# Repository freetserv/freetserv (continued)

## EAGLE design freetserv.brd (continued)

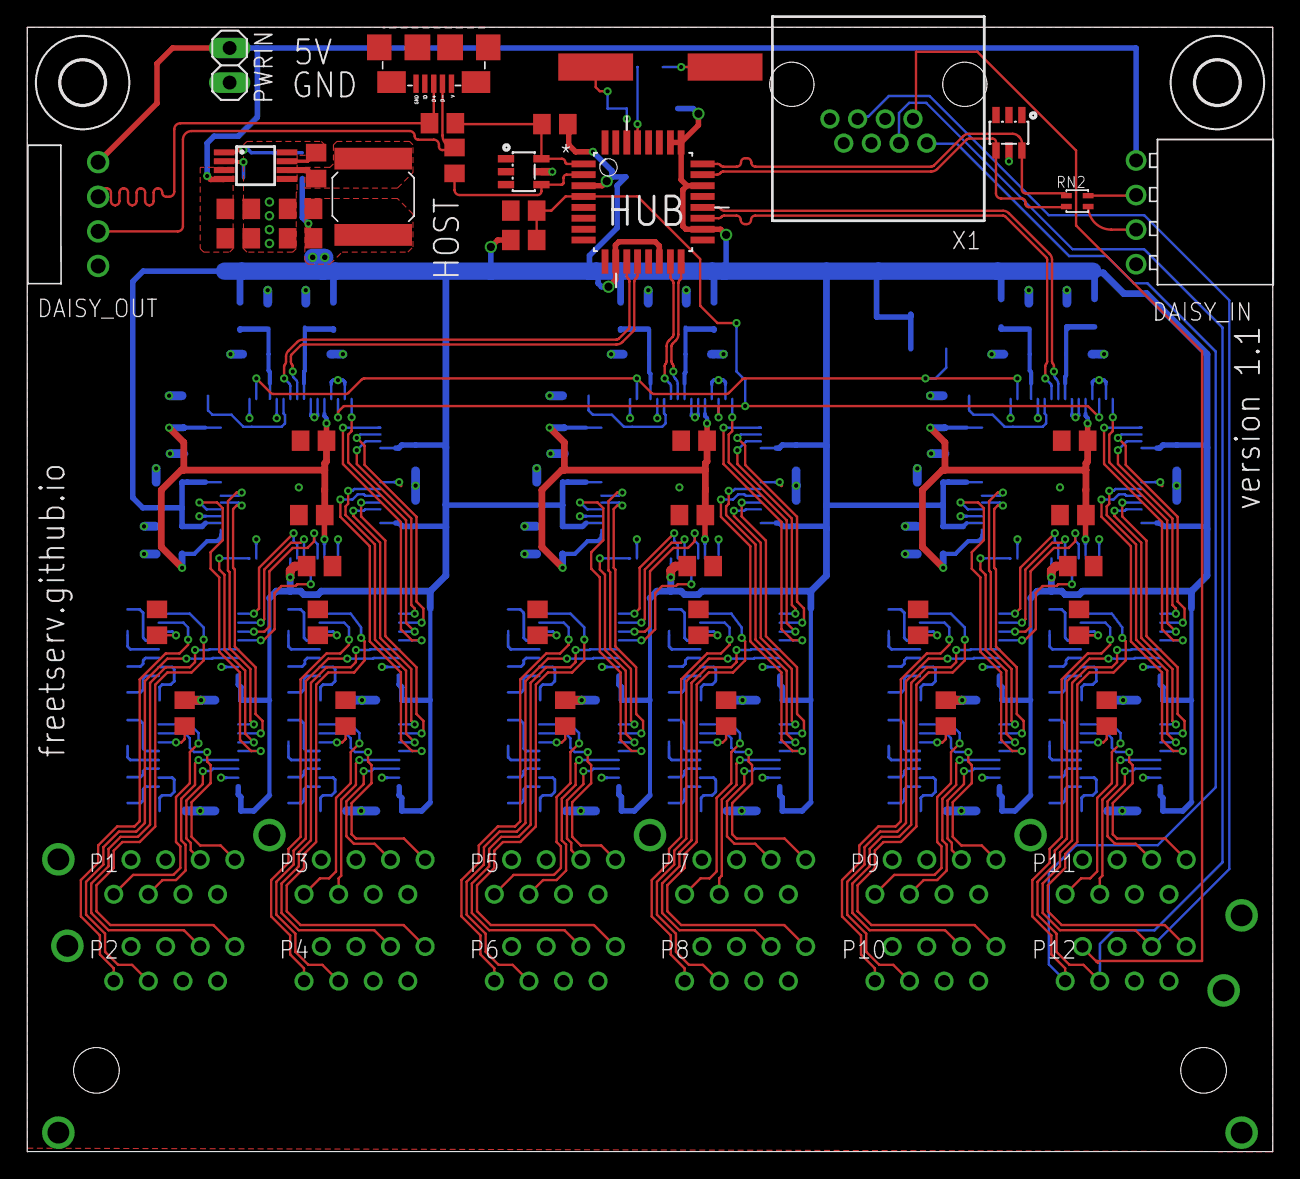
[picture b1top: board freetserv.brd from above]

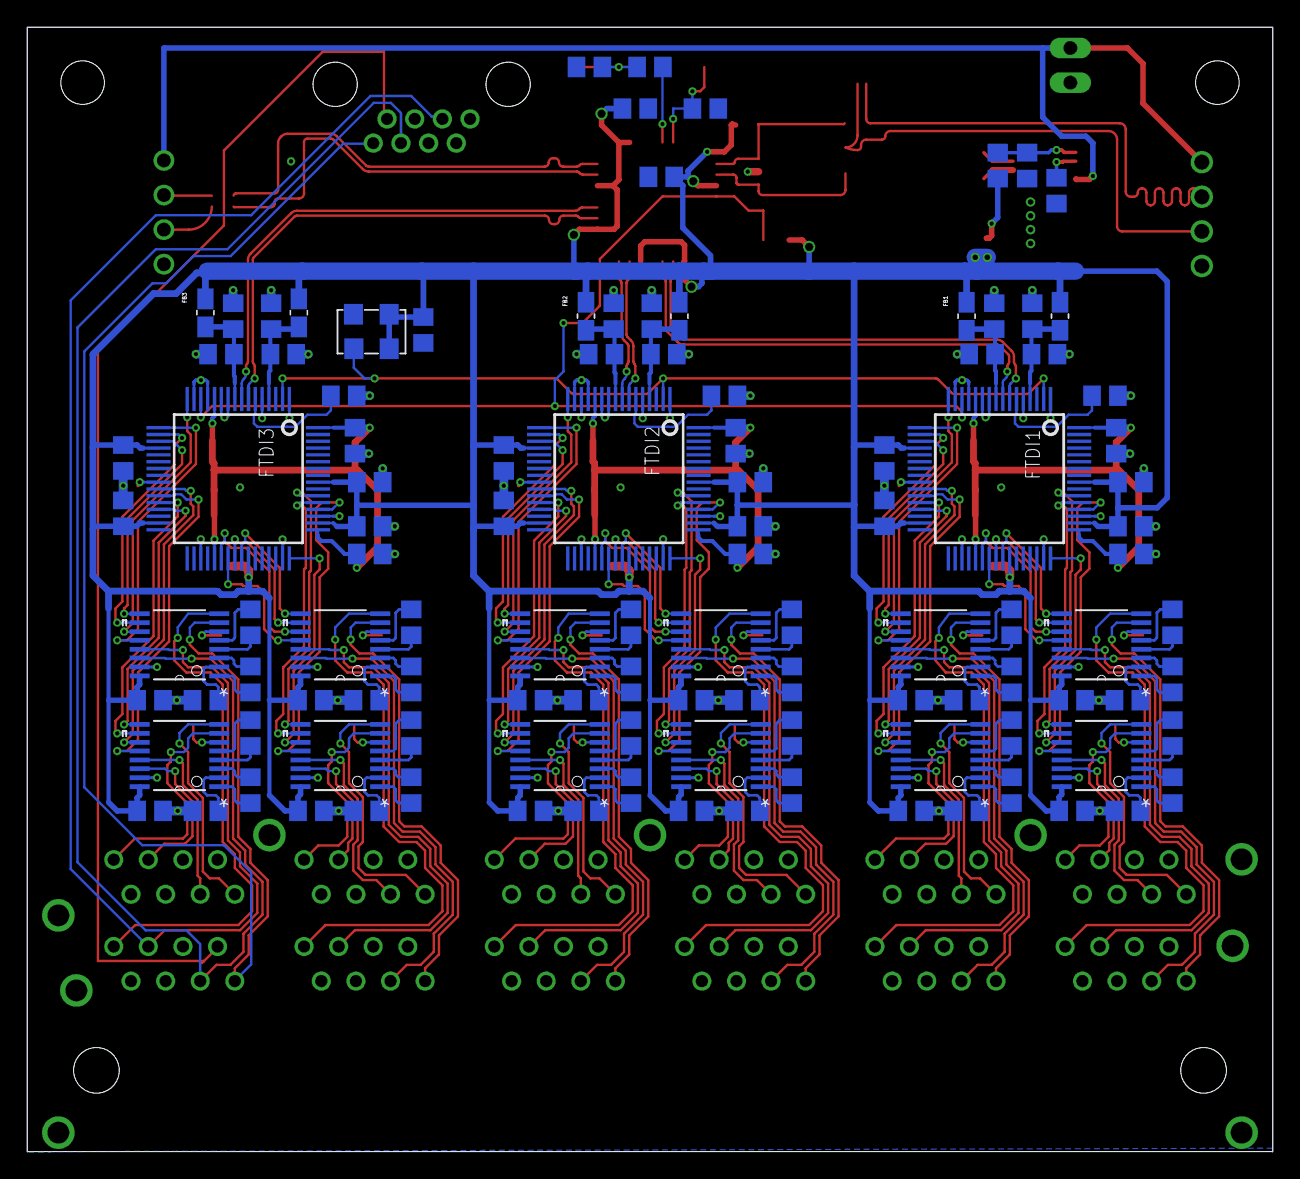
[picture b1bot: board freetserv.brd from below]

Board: 2 copper layers, 91.4 x 82.5 mm, 158 parts (112 on the bottom side), 207 nets.

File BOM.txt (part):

Qty Value              Part Num         Package               Parts                                                                                                                                                                                                                                                                                                                                                                                                                                                                                                       
1                      A1921-ND         1X02                  PWRIN                                                                                                                                                                                                                                                                                                                                                                                                                                                                                                       
95  0.1uF              1276-1003-1-ND   C0805                 C1, C4, C11, C12, C15, C16, C17, C18, C19, C22, C23, C24, C25, C26, C27, C28, C29, C30, C31, C32, C33, C34, C35, C36, C37, C38, C39, C40, C41, C42, C43, C44, C45, C46, C47, C54, C55, C56, C57, C58, C59, C60, C61, C62, C63, C64, C65, C66, C67, C68, C69, C70, C71, C72, C73, C74, C75, C76, C77, C78, C79, C80, C81, C89, C90, C91, C92, C93, C94, C95, C96, C97, C98, C99, C100, C101, C102, C103, C104, C105, C106, C107, C108, C109, C110, C111, C112, C113, C114, C115, C116, C489, C519, C859, C869
2   1.5K               311-1.5KARCT-ND  R0805                 R3, R6                                                                                                                                                                                                                                                                                                                                                                                                                                                                                                      
1   1uF                311-1365-1-ND    C0805                 C5                                                                                                                                                                                                                                                                                                                                                                                                                                                                                                          
3   3.3uF              445-7589-1-ND    C0805                 C8, C629, C829                                                                                                                                                                                                                                                                                                                                                                                                                                                                                              
6   4.7uF              1276-2972-1-ND   C0805                 C13, C14, C53, C502, C879, C889                                                                                                                                                                                                                                                                                                                                                                                                                                                                             
1   6MHz               535-10208-1-ND   CSM-7X-DU             Q2                                                                                                                                                                                                                                                                                                                                                                                                                                                                                                          
1   10k                311-10KARCT-ND   R0805                 R5                                                                                                                                                                                                                                                                                                                                                                                                                                                                                                          
4   10uF               490-10517-1-ND   C0805                 C2, C3, C6, C7                                                                                                                                                                                                                                                                                                                                                                                                                                                                                              
3   12K / 1%           311-12.0KCRCT-ND R0805                 R2, R13, R15                                                                                                                                                                                                                                                                                                                                                                                                                                                                                                
1   15uH               587-2624-1-ND    NR60XX                L3                                                                                                                                                                                                                                                                                                                                                                                                                                                                                                          
2   18pF               709-1171-1-ND    C0805                 C20, C21                                                                                                                                                                                                                                                                                                                                                                                                                                                                                                    
1   22K                311-22KARCT-ND   R0805                 R7                                                                                                                                                                                                                                                                                                                                                                                                                                                                                                          
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
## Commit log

2015-09-01 Initial commit, schematics mostly complete, layout still not done
2015-09-01 layouted power-related part, added more MAX3232 drivers to schematics
2015-09-01 layout all MAX3232s, position power distribution
2015-09-02 routed the MAX3232 and FT4232HL within final space constraints
2015-09-02 use TUSB2046B (+ additional USB port), route both
    Warnings need to be addressed, but the bulk of the routing should now be
    done.
2015-09-03 hook up the second USB port to the SN75240 as well
2015-09-03 make differential pairs more symmetric, move vias close to TUSB
    also add the recommended 0.1uF capacitor close to the power pin
2015-09-03 fix GND plane vias for power USB ports
2015-09-03 fix all clearance DRC warnings (with smart-prototyping DRU file)
2015-09-03 make all vias at least 12mil (minimum smart-prototyping size)
2015-09-03 address all DRC warnings
2015-09-03 add ground planes underneath the crystals
2015-09-03 route the USB data tracks underneath the 3.3V
    That way, we have identical distortions on both lines, and they are
    further away from the voltage regulator.
2015-09-03 add labels to the USB ports
2015-09-03 add .gitignore to ignore EAGLE’s temporary files
2015-09-03 add gerber files for smart-prototyping.com
2015-09-22 renamed L1, L2 to FERRITE1, FERRITE2, added values
2015-09-26 Bugfix: add 1.5kΩ resistor to USB D+ to host
    This is necessary for the host to recognize that a USB device was
    plugged in. Without this resistor, nothing happens when you connect the
    board to a computer.
2015-09-26 Replace all 100nF capacitors with 0.1uF (which is the same)
    Since capacitors are labelled as 0.1uF, this makes it more clear which
    part goes where.
    fixes #8
2015-09-26 use 18pF capacitors to match the crystals
2015-09-26 assign part numbers for almost all parts
    The remaining parts are possibly subject to change.
    This was done using the bom-ex ULP:
    http://www.cadsoftusa.com/downloads/file/bom-ex164.zip
    fixes #10
    fixes #13
    fixes #14
2015-09-26 rename VCC/VCC_3.3V to +5V and +3V3, use appropriate supply pins
    Also disconnect the power supply part from the USB hub so that we have
    an easier time adding the R/C circuit.
2015-09-26 replace volt supervisor IC with R/C circuit
    Not yet routed to the FTDI, because that area still needs some
    re-routing anyway.
    fixes #5
2015-09-26 increase pad sizes of U1
    fixes #3
2015-09-26 increase FTDI pad size
    Will need re-routing, but the FTDI part will need to be redone anyway
    due to issue #11.
    fixes #7
2015-09-26 increase pad size of FERRITE1,2
    fixes #9
2015-09-26 add circle to pin 1 for the MAX3232
    Also use the correct IC (E variant for ESD protection) and rename the
    ICs properly (DRIVER → DRV so that the name fits, suffix 0A-0D like the
    FTDI outputs).
    see issue #2
2015-09-26 add circle to pin 1 of the TUSB2046, increase pad size while at it
    fixes #2
2015-09-28 add capacitors for VCORE/VIO
    fixes #12
2015-09-28 move 100nF capacitors closer to VPHY/VPLL
    fixes #11
2015-09-28 re-route USB as differential pairs with 45° traces
    fixes #1
2015-09-28 add 27Ω resistors to host D+/D- port for impedance matching
    fixes #6
2015-09-28 fix remaining DRC errors
2015-09-28 fix remaining airwires
2015-09-28 add remaining part numbers
2015-09-28 swap all X5R capacitors with X7R ones
2015-09-28 add BOM to git
2015-10-05 wire up the 12-port 8P8C device
2015-10-06 wire up a serial port
2015-10-06 Bugfix: disconnect EEDATA/EECS from GND (Thanks Volker!)
    With this fix, the FTDI converter is recognized by the host \o/
2015-11-08 Volker re-organized the schematics
2015-11-08 Volker re-routed the FTDI (work-in-progress)
2015-11-08 Volker finished the FTDI routing, duplicated it
2015-11-08 replace micro-USB power input with 2-pin header
2015-11-08 add daisy-chain input/output socket/pin headers
2015-11-08 drc: fix via size, width on bottom layer
2015-11-08 fix drc warnings in power supply
2015-11-08 wire up power supply
2015-11-08 wire up USB hub
2015-11-08 fix all airwires except from the USB differential pair
2015-11-08 wire up DAISY_OUT
2015-11-08 add tPlace documentation (port descriptions, version)
2015-11-08 re-route DAISY_OUT’s USB traces
2015-11-08 update part numbers and BOM
2015-11-08 fix clearance DRC error
2015-11-09 import Schaeffer AG’s “Side Profile 1”
    See http://www.schaeffer-ag.de/en/products/housings/
    The file was downloaded from
    http://www.schaeffer-ag.de/fileadmin/user_upload/Geh%C3%A4use/Zips/Side-profile-1.zip
2015-11-09 reduce depth to 150mm
2015-11-09 add M2.5 drill holes for the freetserv PCBs
2015-11-09 add holes for the 8P8C connectors
2015-11-09 add mounting holes for the raspberry pi
2015-11-09 add mount holes for the PSU
2015-11-09 add hole for the power plug
2015-11-09 add text
2015-11-09 added fan to back plate
2015-11-20 swap crystal part number to FOX924B-12.000 (old one was too big)
    fixes #17
2015-11-21 back plate: replace 40x40mm fan hole with 30x30mm fan hole
2015-11-21 silkscreen: move labels so they are clearly visible
    I didn’t enable vector font rendering previously, so on the manufactured
    PCB, some labels are cut off.
2015-11-21 reduce pin 1 circle size on the MAX3232 ICs
2015-11-21 replace M2.5 drill holes with M3 for freetserv PCBs
    …so that they match the drill holes in the PCB, which are M3.
2015-11-21 split top+bottom into separate top and bottom files
    The top plate does not need all the drill holes (cheaper/cleaner).
2015-11-22 bottom: duplicate M3 drill holes, so there are 2 positions for the PSU
    We’ll see which one works better. Also move the raspberry pi a bit more
    to the right, so that there is some space between the PSU and the
    raspberry pi.
2015-11-27 freetserv.sch: fix broken forward/backward-annotation
    caused by commit 1419bf359ab668af9a7b72a02ff99d9803568ba5, where I
    forgot to also commit the changes to the .sch file.
2015-11-27 add eagle project file stub
    This way, after cloning freetserv, you can add the path to
    Options → Directories in eagle.
2015-11-27 bottom: move PSU and raspberry pi a little to the right
    The old position obscured the fan and the micro USB port.
2015-11-27 top/bottom: add 2mm of material
    …so that the plates can slide into the front plate.
2015-11-27 move raspberry pi even further to the right
    This way, we have a chance to use all 3 angles for the case.
2015-11-27 front: move slide-in space by 1mm each to fit the side profile
2015-11-27 front: fix power inlet cutout dimensions
2015-11-27 front: add labels for power inlet and ports
2015-11-27 enlarge bottom/top plate by 2cm
    This gives us enough space to, if we have to, connect each individual
    PCB via USB to the raspberry pi. It also makes sure that the power
    supply has the recommended safety distance of 4mm on all sides. Further,
    we should be able to use all the angles in the case now.
2015-11-27 bottom: move PCB mounting holes to the left
2015-11-27 front: add 5mm hole for power LED
    this concludes the changes for revision 2 of the case
    fixes #20
2015-11-29 Bugfix: pin 4 of DAISY_IN was not properly connected to GND
2015-11-30 enable alwaysvectorfont
2015-11-30 clean up silk screen on the top layer
    see issue #24
2015-11-30 clean up silk screen on the bottom layer
    see issue #24
2015-11-30 import smart-prototyping’s EagleCAM.cam
2015-11-30 dos2unix EagleCAM.cam
2015-11-30 cam: silk screen: enable top/bottom values
    fixes #24
2015-11-30 increase ferrite pad sizes for easier hand-soldering
    fixes #19
2015-11-30 swap oscillator with ASFL1-12.000MHZ-EK-T
    The new one has little holes in the sides, making hand-soldering
    possible.
    see #18
2015-11-30 increase pad size of the oscillator for easier hand-soldering
    fixes #18
2015-11-30 bump PCB version to 1.1
2015-12-07 top/bottom/back: remove middle housing bracket holes
    These cannot be used because of the PSU, so there’s no point in keeping
    them around.
    fixes #28
2015-12-07 top plate: place cut-out on the back side
    fixes #27
2015-12-10 front: undo moving slide-in cutout
    Turns out I misunderstood how the top/bottom plate are supposed to slide
    into the case.
    This reverts 53688bf7ae2e356861aa1cd1da1d178a7d0fdc75
    issue #33 is related
2015-12-10 top: place cut-outs on the front side again
    This reverts commit f9b77c2f7ac78431a26ba20b34ed945c98553213
    issue #33 is related
2015-12-10 bottom: fix cutouts and sink holes (need to go onto the back side)
    fixes #33
2015-12-10 front: allow for both, snap-in and screw-mounted power inlets
    fixes #29
2015-12-10 front: add another 5mm LED hole for a watchdog LED, add labels
    issue #30 is related
2015-12-10 Add udev rules file.
    fixes #25
2015-12-10 Add watchdog which toggles GPIO4 every second.
    A +3.3V LED (with appropriate resistor to limit the current to 10mA) can
    be connected to GPIO4 and serve as a watchdog LED, i.e. to indicate the
    device is still working.
2015-12-11 add fts-adduser and fts-port-owner wrapper scripts, add motd
2015-12-12 add trivial LED PCB, change front plate accordingly
    You can solder the two LEDs (1497-1017-ND on digikey) onto the PCB, then
    mount the PCB onto the front plate using two M3 screws (335-1150-ND on
    digikey), possibly with one or two fasteners (H767-ND on digikey).
    This change makes all parts use screws (the LED was glued to the front
    plate previously).
    issue #30 is related
2015-12-12 gitignore: ignore eagle lock files and frontdesign backup files
2015-12-12 bottom plate: use threaded inserts instead of threaded holes
    This makes the bottom plate 10€ more expensive, but frees us from
    hand-shortening M3 hex standoffs (because they are not available with
    the length we need them in).
2015-12-13 front: fix PCB LED dimensions, fix power inlet cutout
    The power inlet cutout is for the
    Delta Electronics 03GEEW3E (Digi-Key 1144-1024-ND)
2015-12-24 add LICENSE file (CERN Open Hardware License 1.2)
2016-01-15 motd: need to use /home/${NEWUSER}, ~${NEWUSER} does not work
2016-03-03 tweaked by jaredmauch
2016-04-04 front plate: move LEDs .5mm to the top, 1mm to the right
    That way, they don’t conflict with the PCB.
2016-10-19 Update text-format BOM
    fixes #41
2020-05-15 add rules for USB on Raspi 4
    Raspi 4 has platform-fd500000.pcie-pci-0000:01:00.0-usb-[0-9] instead of platform-bcm2708_usb-usb-[0-9].
    Having rules for Raspi 2 and 4 create (and remove) the same symlinks should be fine as only one of the rules matches and as long as there is a match, the symlink gets created.
2020-05-15 add rules for USB on Raspi 4 (#47)
    Raspi 4 has platform-fd500000.pcie-pci-0000:01:00.0-usb-[0-9] instead of platform-bcm2708_usb-usb-[0-9].
    Having rules for Raspi 2 and 4 create (and remove) the same symlinks should be fine as only one of the rules matches and as long as there is a match, the symlink gets created.
